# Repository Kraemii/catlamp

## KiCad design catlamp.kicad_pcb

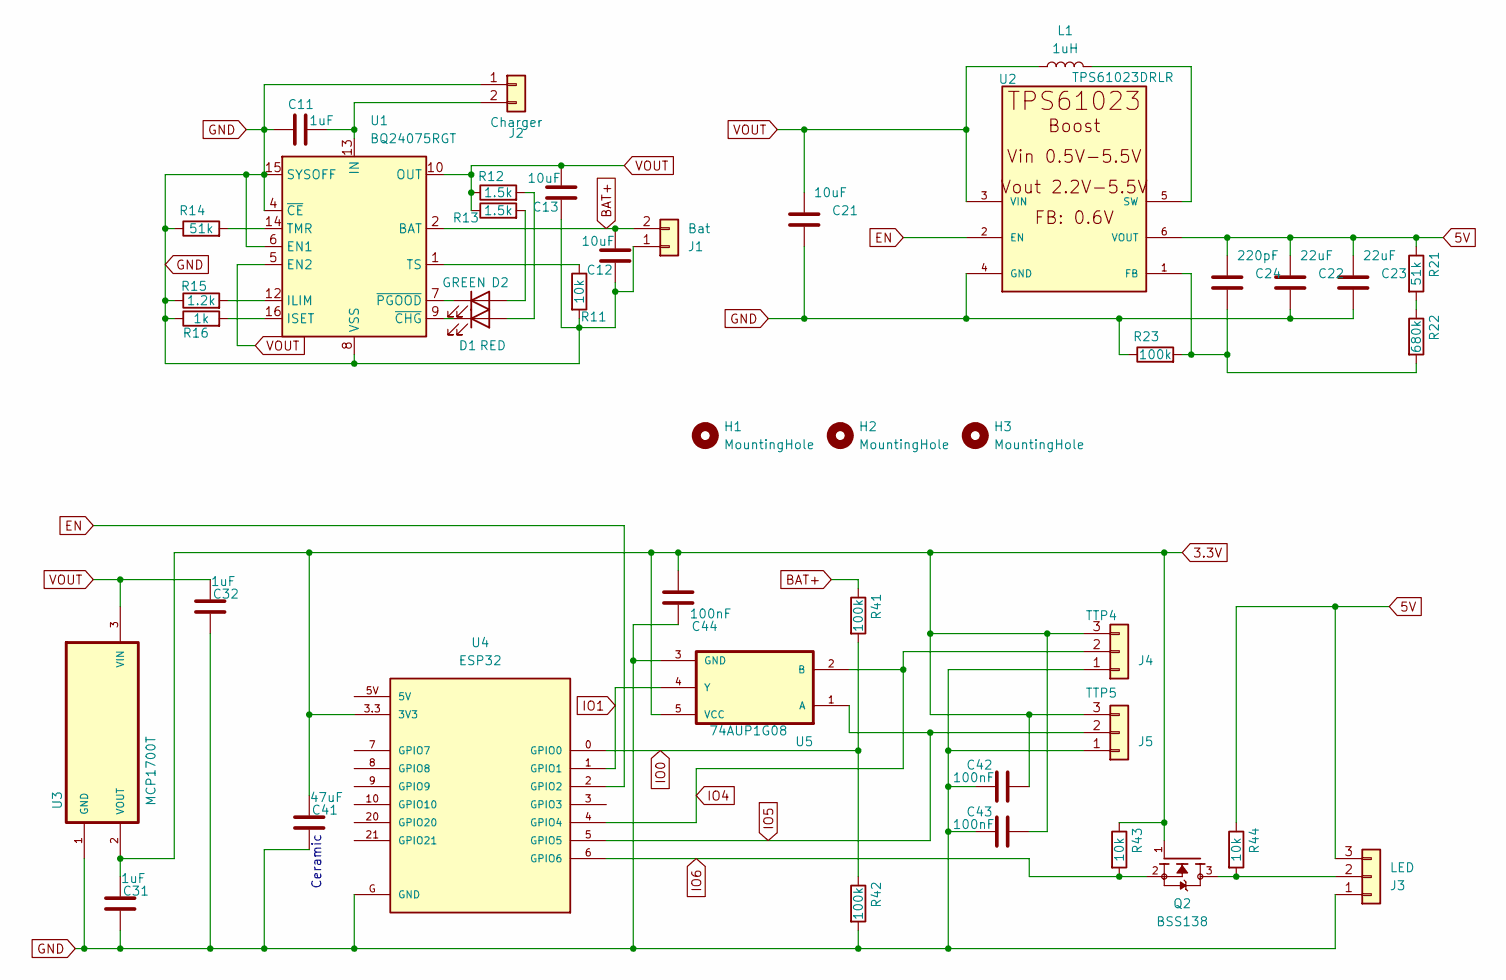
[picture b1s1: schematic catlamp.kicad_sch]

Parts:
C11, C31, C32: 1uF; C_0805_2012Metric_Pad1.18x1.45mm_HandSolder
C12, C13, C21: 10uF; C_0805_2012Metric_Pad1.18x1.45mm_HandSolder
C22, C23: 22uF; C_0805_2012Metric_Pad1.18x1.45mm_HandSolder
C24: 220pF; C_0805_2012Metric_Pad1.18x1.45mm_HandSolder
C41: 47uF; C_0805_2012Metric_Pad1.18x1.45mm_HandSolder
C42, C43, C44: 100nF; C_0805_2012Metric_Pad1.18x1.45mm_HandSolder
D1: RED; LED_0805_2012Metric_Pad1.15x1.40mm_HandSolder
D2: GREEN; LED_0805_2012Metric_Pad1.15x1.40mm_HandSolder
H1, H2, H3: MountingHole; MountingHole_2.2mm_M2
J1: Bat; PinHeader_1x02_P2.54mm_Vertical
J2: Charger; PinHeader_1x02_P2.54mm_Vertical
J3: LED; JST_PH_B3B-PH-K_1x03_P2.00mm_Vertical
J4: TTP4; JST_PH_B3B-PH-K_1x03_P2.00mm_Vertical
J5: TTP5; JST_PH_B3B-PH-K_1x03_P2.00mm_Vertical
L1: 1uH; L_APV_APH0630
Q2: BSS138; SOT-23_Handsoldering; PARTREV 30 Jan 2018
R11, R43, R44: 10k; R_0805_2012Metric_Pad1.20x1.40mm_HandSolder
R12, R13: 1.5k; R_0805_2012Metric_Pad1.20x1.40mm_HandSolder
R14, R21: 51k; R_0805_2012Metric_Pad1.20x1.40mm_HandSolder
R15: 1.2k; R_0805_2012Metric_Pad1.20x1.40mm_HandSolder
R16: 1k; R_0805_2012Metric_Pad1.20x1.40mm_HandSolder
R22: 680k; R_0805_2012Metric_Pad1.20x1.40mm_HandSolder
R23, R41, R42: 100k; R_0805_2012Metric_Pad1.20x1.40mm_HandSolder
U1: BQ24075RGT; VQFN-16-1EP_3x3mm_P0.5mm_EP1.6x1.6mm
U2: TPS61023DRLR; SOT563-ORI
U3: MCP1700T; SOT-23_Handsoldering
U4: ESP32; MODULE_ESP32-C3_SUPERMINI
U5: 74AUP1G08; SOT-23-5_HandSoldering

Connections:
3.3V: C31.1, C41.1, C42.2, C43.2, C44.2, J4.3, J5.3, Q2.1, R43.1, U3.2 (VOUT), U4.3.3 (3V3), U5.5 (VCC)
5V: C22.1, C23.1, C24.1, J3.3, R21.1, R44.1, U2.6 (VOUT)
BAT+: C12.2, J1.2, R41.1, U1.2 (BAT), U1.3 (BAT)
EN: U2.2 (EN), U4.2 (GPIO2)
GND: C11.1, C12.1, C13.1, C21.2, C22.2, C23.2, C31.2, C32.2, C41.2, C42.1, C43.1, C44.1, J1.1, J2.1, J3.1, J4.1, J5.1, R11.2, R14.1, R15.1, R16.1, R23.1, R42.2, U1.4 (~CE), U1.6 (EN1), U1.8 (VSS), U1.15 (SYSOFF), U1.17 (VSS), U2.4 (GND), U3.1 (GND), U4.G (GND), U5.3 (GND)
IO0: R41.2, R42.1, U4.0 (GPIO0)
IO1: U4.1 (GPIO1), U5.4 (Y)
IO4: J4.2, U4.4 (GPIO4), U5.2 (B)
IO5: J5.2, U4.5 (GPIO5), U5.1 (A)
IO6: Q2.2, R43.2, U4.6 (GPIO6)
unnamed: D1.2 (A), R12.2
unnamed: D1.1 (K), U1.9 (~CHG)
unnamed: D2.2 (A), R13.2
unnamed: D2.1 (K), U1.7 (~PGOOD)
unnamed: C11.2, J2.2, U1.13 (IN)
unnamed: J3.2, Q2.3, R44.2
unnamed: R21.2, R22.1
unnamed: R15.2, U1.12 (ILIM)
unnamed: R16.2, U1.16 (ISET)
unnamed: R14.2, U1.14 (TMR)
unnamed: R11.1, U1.1 (TS)
unnamed: C24.2, R22.2, R23.2, U2.1 (FB)
unnamed: L1.2, U2.5 (SW)
VOUT: C13.2, C21.1, C32.1, L1.1, R12.1, R13.1, U1.5 (EN2), U1.10 (OUT), U1.11 (OUT), U2.3 (VIN), U3.3 (VIN)

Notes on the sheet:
Ceramic

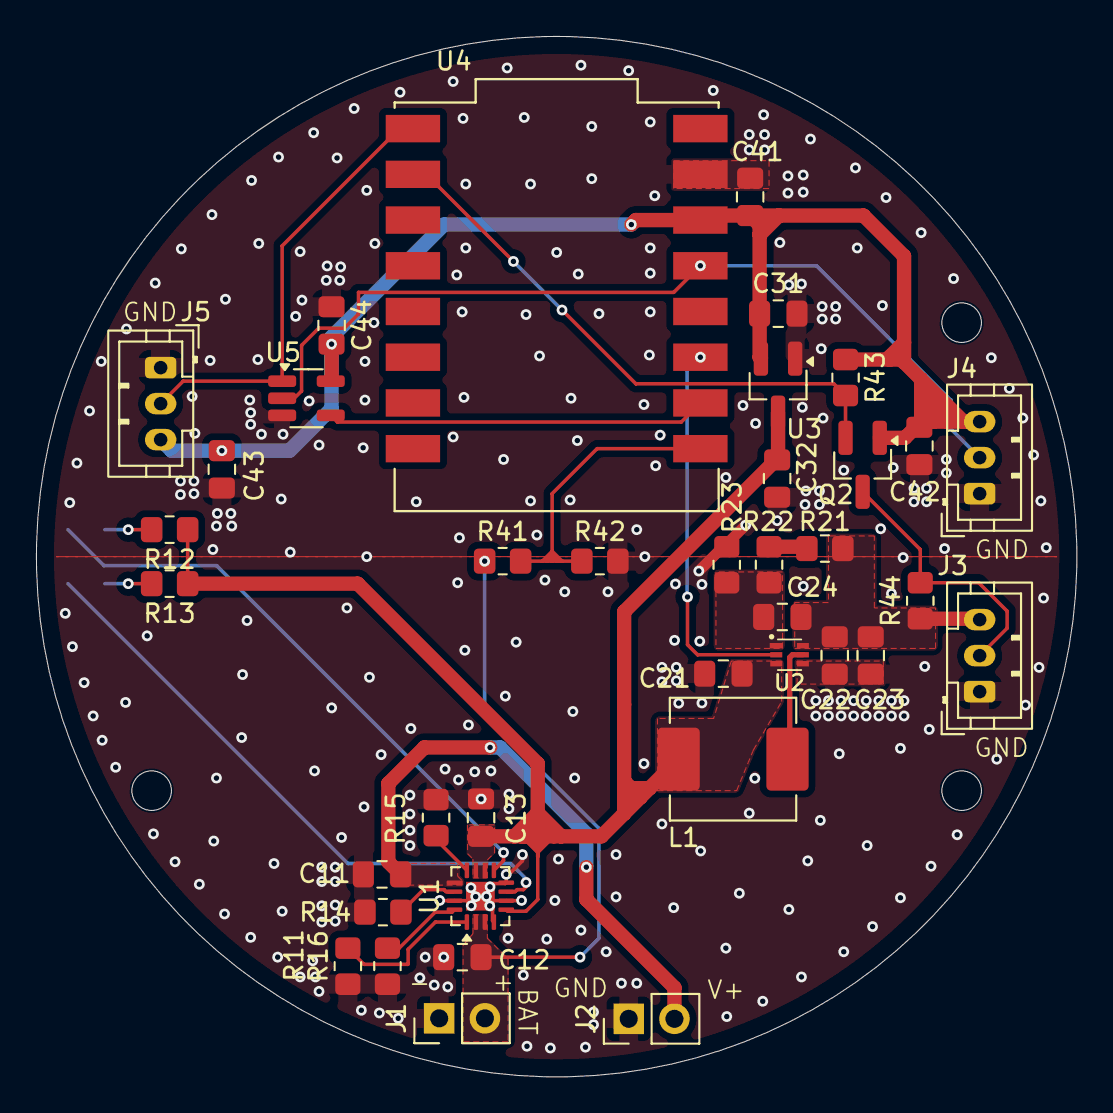
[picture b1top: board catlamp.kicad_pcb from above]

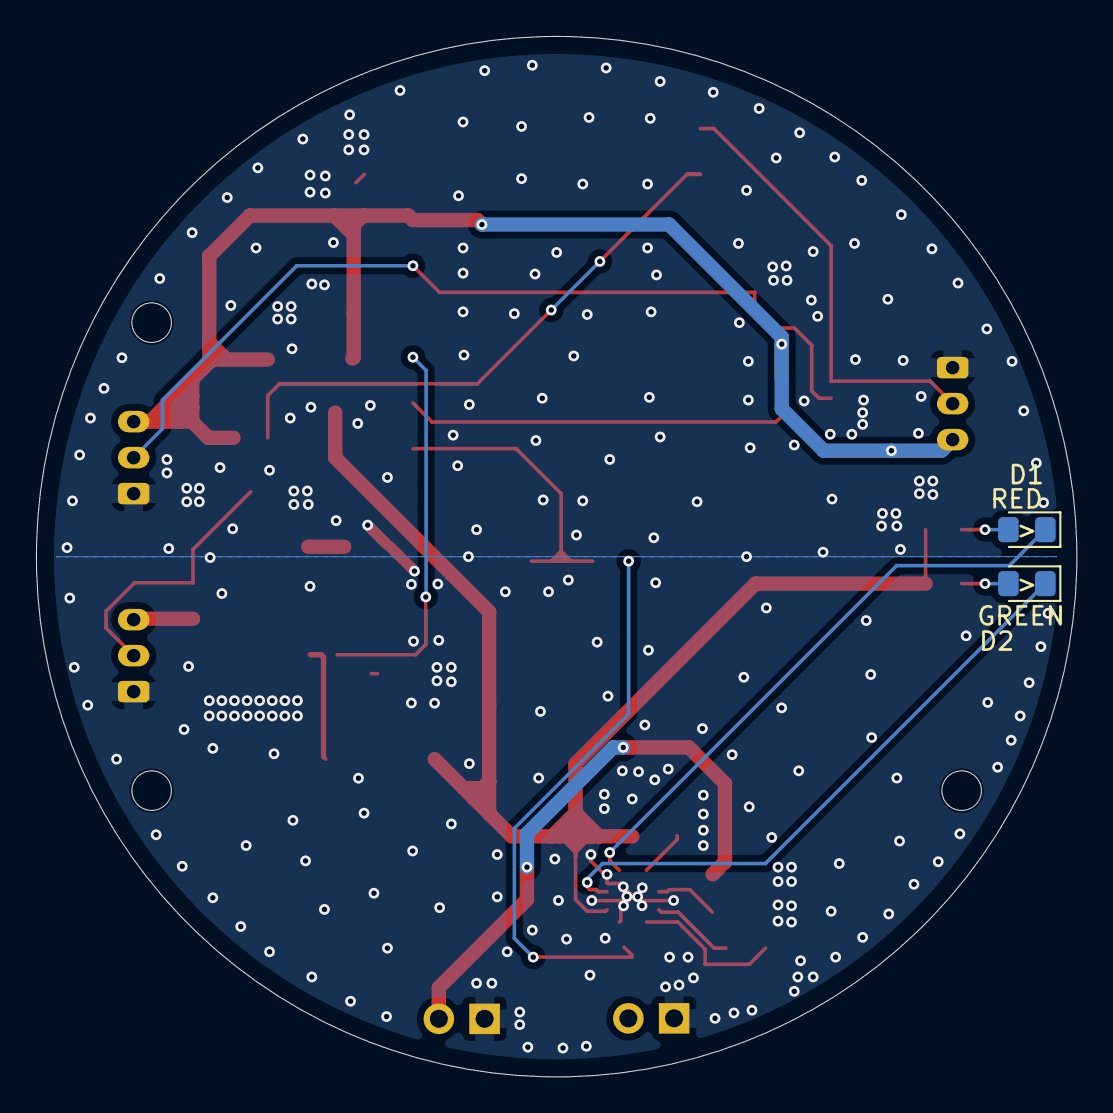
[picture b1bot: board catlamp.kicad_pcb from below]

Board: 2 copper layers, 57.8 x 57.8 mm, 46 parts (2 on the bottom side), 24 nets.

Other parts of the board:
H1#2: MountingHole; MountingHole_2.2mm_M2
H2#2, H3#2: Conn_01x01_MountingPin; MountingHole_2.2mm_M2
